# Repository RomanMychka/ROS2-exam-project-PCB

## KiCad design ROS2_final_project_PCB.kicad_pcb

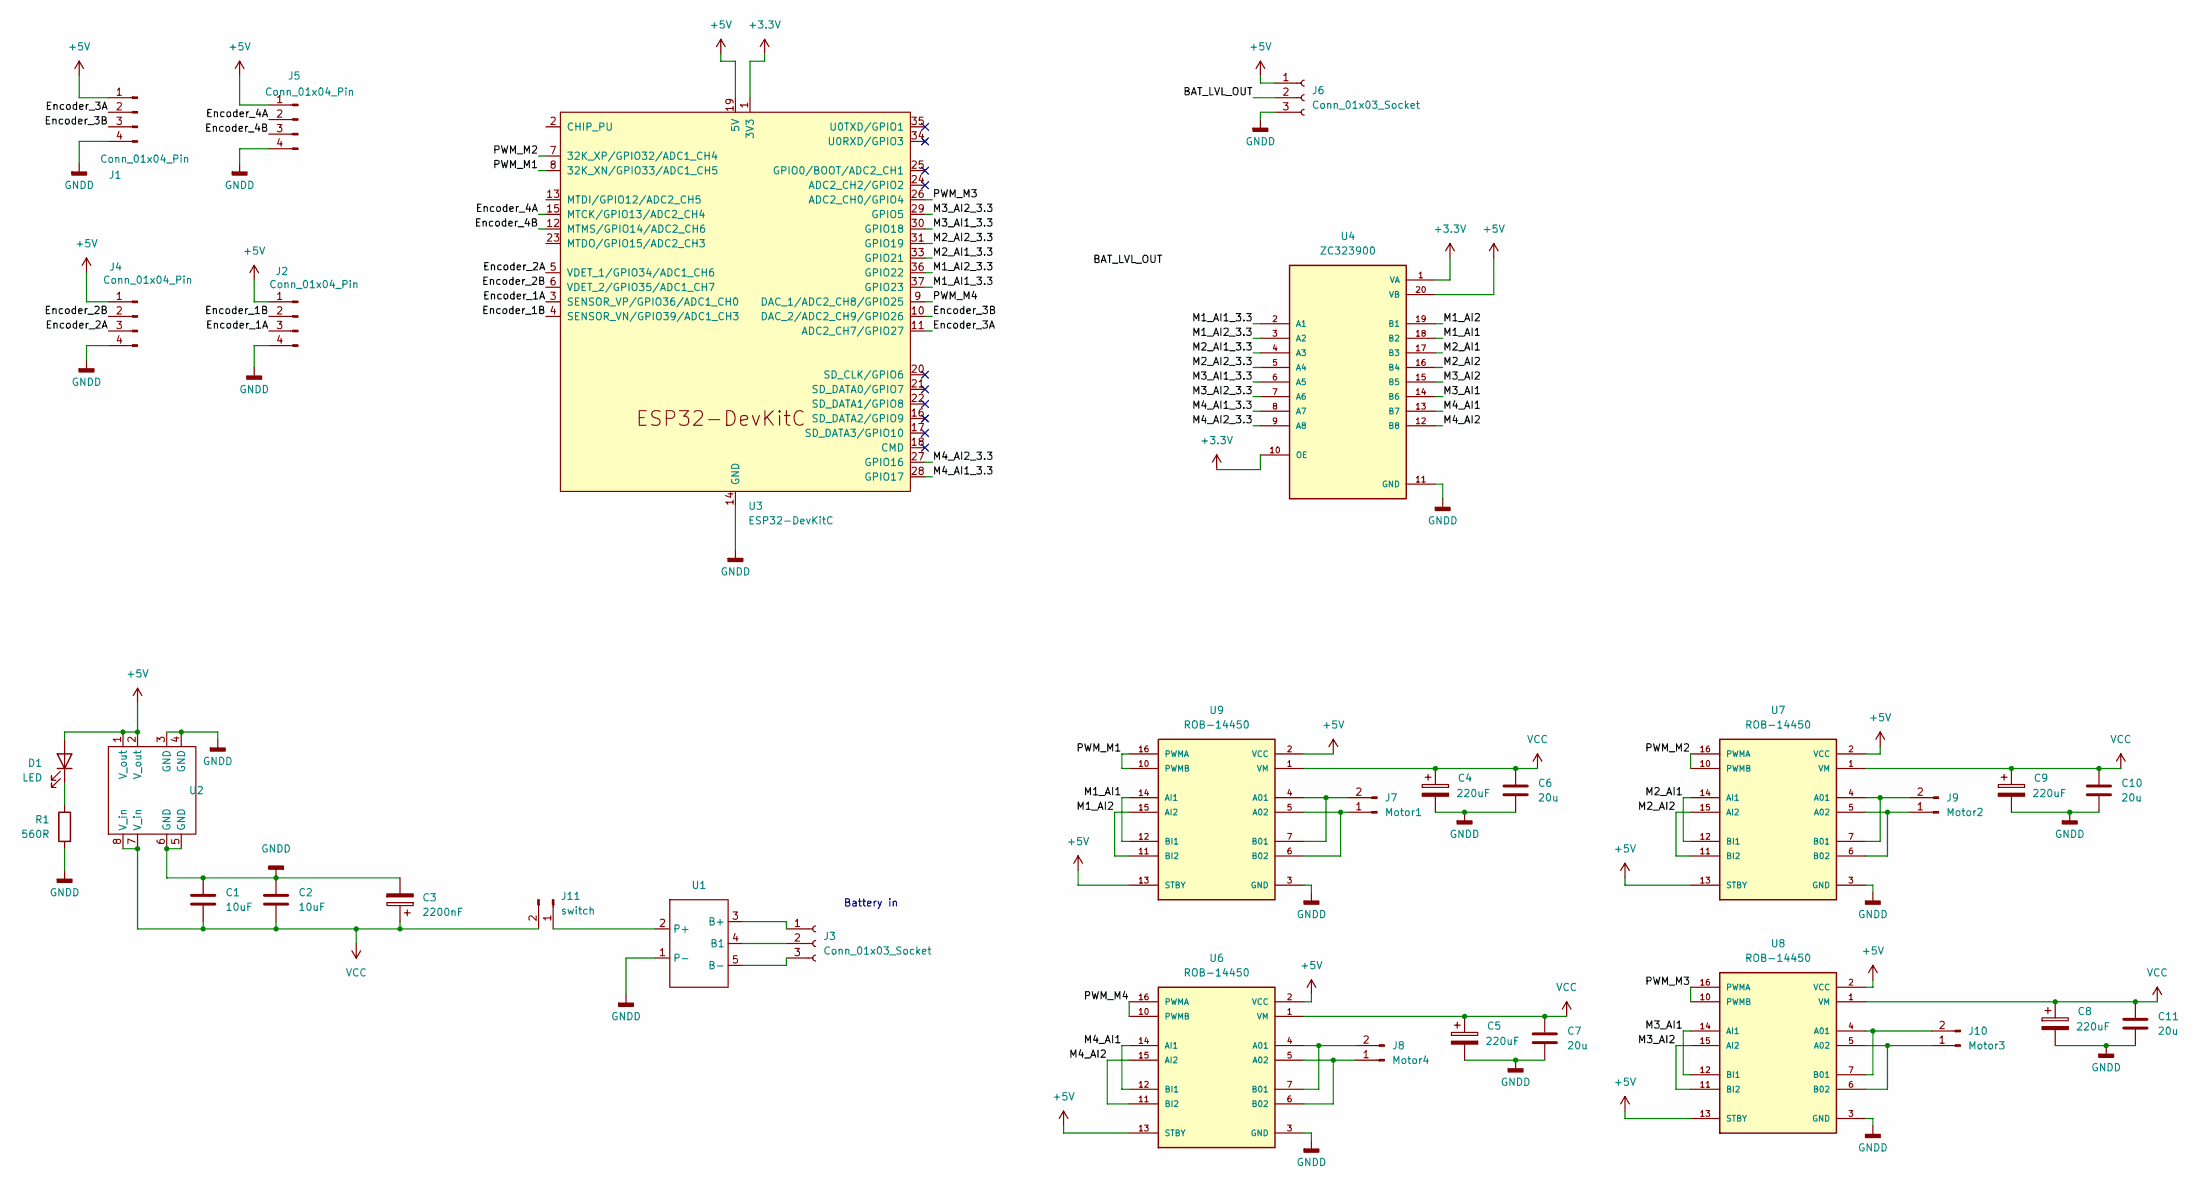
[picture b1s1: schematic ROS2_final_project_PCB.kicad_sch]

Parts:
C1, C2: 10uF; C_Disc_D3.0mm_W1.6mm_P2.50mm
C3: 2200nF; C_Radial_D12.5mm_H20.0mm_P5.00mm
C4, C5, C8, C9: 220uF; CP_Radial_D13.0mm_P5.00mm
C6, C7, C10, C11: 20u; C_Disc_D4.3mm_W1.9mm_P5.00mm
D1: LED; LED_D3.0mm
J1, J2, J4, J5: Conn_01x04_Pin; JST_PH_B4B-PH-K_1x04_P2.00mm_Vertical
J3: Conn_01x03_Socket; FanPinHeader_1x03_P2.54mm_Vertical
J6: Conn_01x03_Socket; PinSocket_1x03_P2.00mm_Vertical
J7: Motor1; Molex_KK-254_AE-6410-02A_1x02_P2.54mm_Vertical
J8: Motor4; Molex_KK-254_AE-6410-02A_1x02_P2.54mm_Vertical
J9: Motor2; Molex_KK-254_AE-6410-02A_1x02_P2.54mm_Vertical
J10: Motor3; Molex_KK-254_AE-6410-02A_1x02_P2.54mm_Vertical
J11: switch; Molex_KK-254_AE-6410-02A_1x02_P2.54mm_Vertical
R1: 560R; R_Axial_DIN0204_L3.6mm_D1.6mm_P7.62mm_Horizontal
U1: BMS ROS2 project
U2: Buck convertor
U3: ESP32-DevKitC
U4: ZC323900; MODULE_ZC323900; PARTREV NA
U6, U7, U8, U9: ROB-14450; MODULE_ROB-14450; PARTREV 11-13-17

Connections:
+3.3V: U3.1 (3V3), U4.1 (VA), U4.10 (OE); also elsewhere on the board
+5V: D1.2 (A), J1.1, J2.1, J4.1, J5.1, J6.1, U2.1 (V_out), U2.2 (V_out), U3.19 (5V), U4.20 (VB), U6.2 (VCC), U6.13 (STBY), U7.2 (VCC), U7.13 (STBY), U8.2 (VCC), U8.13 (STBY), U9.2 (VCC), U9.13 (STBY)
/BAT_LVL_OUT: J6.2
/Encoder_1A: J2.3, U3.3 (SENSOR_VP/GPIO36/ADC1_CH0)
/Encoder_1B: J2.2, U3.4 (SENSOR_VN/GPIO39/ADC1_CH3)
/Encoder_2A: J4.3, U3.5 (VDET_1/GPIO34/ADC1_CH6)
/Encoder_2B: J4.2, U3.6 (VDET_2/GPIO35/ADC1_CH7)
/Encoder_3A: J1.2, U3.11 (ADC2_CH7/GPIO27)
/Encoder_3B: J1.3, U3.10 (DAC_2/ADC2_CH9/GPIO26)
/Encoder_4A: J5.2, U3.15 (MTCK/GPIO13/ADC2_CH4)
/Encoder_4B: J5.3, U3.12 (MTMS/GPIO14/ADC2_CH6)
/M1_AI1: U4.18 (B2), U9.12 (BI1), U9.14 (AI1)
/M1_AI1_3.3: U3.37 (GPIO23), U4.2 (A1)
/M1_AI2: U4.19 (B1), U9.11 (BI2), U9.15 (AI2)
/M1_AI2_3.3: U3.36 (GPIO22), U4.3 (A2)
/M2_AI1: U4.17 (B3), U7.12 (BI1), U7.14 (AI1)
/M2_AI1_3.3: U3.33 (GPIO21), U4.4 (A3)
/M2_AI2: U4.16 (B4), U7.11 (BI2), U7.15 (AI2)
/M2_AI2_3.3: U3.31 (GPIO19), U4.5 (A4)
/M3_AI1: U4.14 (B6), U8.12 (BI1), U8.14 (AI1)
/M3_AI1_3.3: U3.30 (GPIO18), U4.6 (A5)
/M3_AI2: U4.15 (B5), U8.11 (BI2), U8.15 (AI2)
/M3_AI2_3.3: U3.29 (GPIO5), U4.7 (A6)
/M4_AI1: U4.13 (B7), U6.12 (BI1), U6.14 (AI1)
/M4_AI1_3.3: U3.28 (GPIO17), U4.8 (A7)
/M4_AI2: U4.12 (B8), U6.11 (BI2), U6.15 (AI2)
/M4_AI2_3.3: U3.27 (GPIO16), U4.9 (A8)
/PWM_M1: U3.8 (32K_XN/GPIO33/ADC1_CH5), U9.10 (PWMB), U9.16 (PWMA)
/PWM_M2: U3.7 (32K_XP/GPIO32/ADC1_CH4), U7.10 (PWMB), U7.16 (PWMA)
/PWM_M3: U3.26 (ADC2_CH0/GPIO4), U8.10 (PWMB), U8.16 (PWMA)
/PWM_M4: U3.9 (DAC_1/ADC2_CH8/GPIO25), U6.10 (PWMB), U6.16 (PWMA)
GNDD: C1.1, C2.1, C3.2, C4.2, C5.2, C6.2, C7.2, C8.2, C9.2, C10.2, C11.2, J1.4, J2.4, J4.4, J5.4, J6.3, R1.2, U1.1 (P-), U2.3 (GND), U2.4 (GND), U2.5 (GND), U2.6 (GND), U3.14 (GND), U3.32 (GND), U3.38 (GND), U4.11 (GND), U6.3 (GND), U6.8 (GND), U6.9 (GND), U7.3 (GND), U7.8 (GND), U7.9 (GND), U8.3 (GND), U8.8 (GND), U8.9 (GND), U9.3 (GND), U9.8 (GND), U9.9 (GND)
unnamed: D1.1 (K), R1.1
unnamed: J3.1, U1.3 (B+)
unnamed: J3.2, U1.4 (B1)
unnamed: J3.3, U1.5 (B-)
unnamed: J7.1, U9.5 (A02), U9.6 (B02)
unnamed: J7.2, U9.4 (A01), U9.7 (B01)
unnamed: J8.1, U6.5 (A02), U6.6 (B02)
unnamed: J8.2, U6.4 (A01), U6.7 (B01)
unnamed: J9.1, U7.5 (A02), U7.6 (B02)
unnamed: J9.2, U7.4 (A01), U7.7 (B01)
unnamed: J10.1, U8.5 (A02), U8.6 (B02)
unnamed: J10.2, U8.4 (A01), U8.7 (B01)
unnamed: J11.1, U1.2 (P+)
VCC: C1.2, C2.2, C3.1, C4.1, C5.1, C6.1, C7.1, C8.1, C9.1, C10.1, C11.1, J11.2, U2.7 (V_in), U2.8 (V_in), U6.1 (VM), U7.1 (VM), U8.1 (VM), U9.1 (VM)

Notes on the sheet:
Battery in

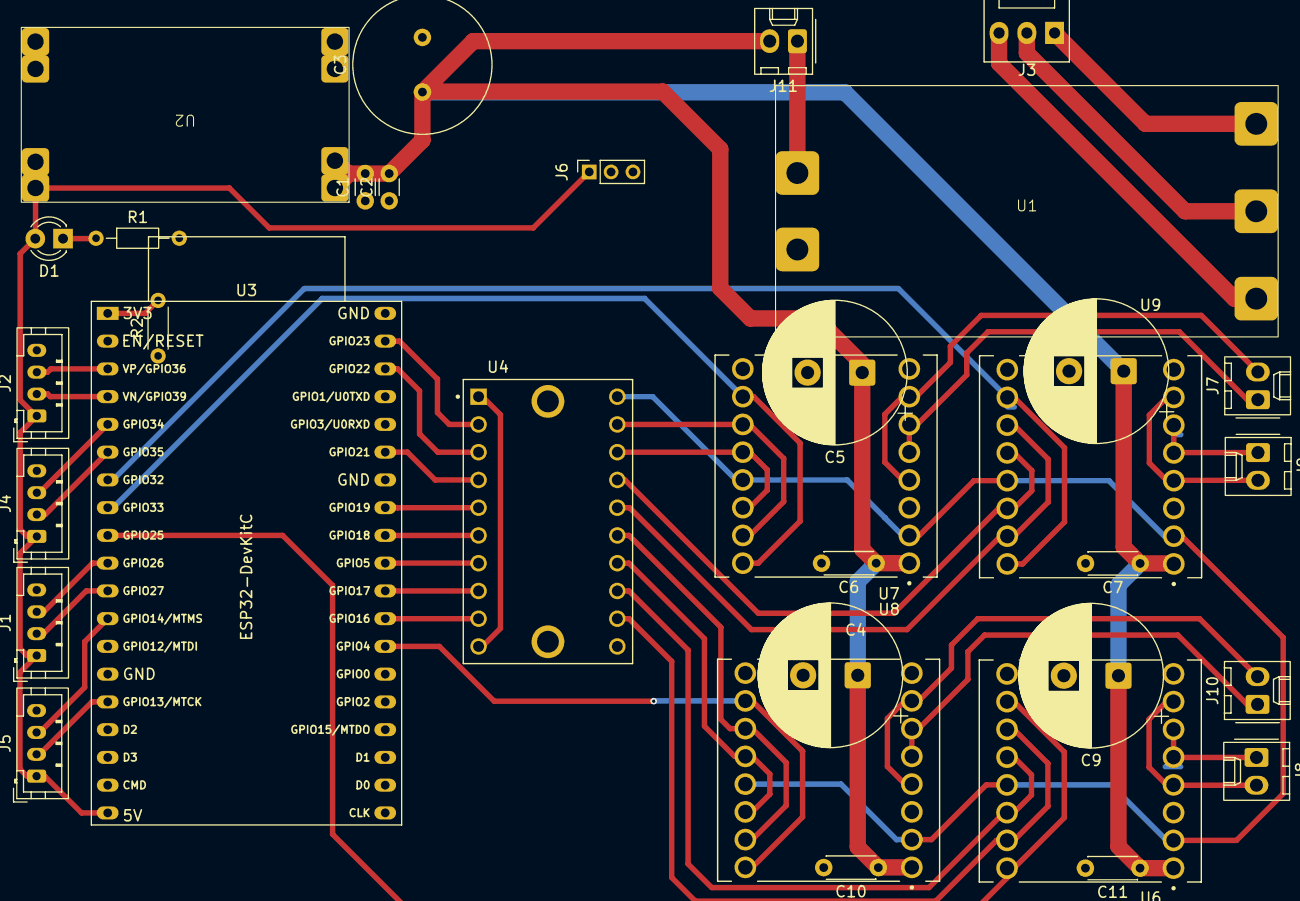
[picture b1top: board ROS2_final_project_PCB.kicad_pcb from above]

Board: 2 copper layers, 33 parts (0 on the bottom side), 45 nets.

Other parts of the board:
R2: 10К; R_Axial_DIN0204_L3.6mm_D1.6mm_P5.08mm_Horizontal

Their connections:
+3.3V: R2.2; also elsewhere on the board
